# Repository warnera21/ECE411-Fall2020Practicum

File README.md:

# ECE411-Fall2020Practicum
This project is based in adding security and ease of access trough a door using Facial Recognition and RFID technologies. The implementation of keeping track of how many (Authorized) user go inside/out of a building is an extra feature that can aid with companies enforcing distancing strategies for COVID purposes. 

### TEAM 8: Hamed AlSaegui, Anthony Warner, Josh Pradera and Tamar Stigler-Flores.

### Arduino Code

	==> if the code is not uploaded yet
		the file (411.ino) must be inside a folder named (411)
		Follow the ... for board connections
		compile and upload the programm to the ATMega chip.
		
	==> used libraries
		SPI.h
		MFRC522.h
		LiquidCrystal_I2C.h
		Wire.h
	==> High Level Diagram Code
		set the LCD address to 0x27 for a 16 chars and 2 line display
		initialize the lcd
		initialize counter
		initialize receiveEvent function
			receive byte as a character
		VOID SETUP
			Initiate I2C communication
			Initiate  address bus designated to I2C with Raspberry Pi
			Initiate each MFRC522 card
			Join I2C bus as slave with address 8
				Call receiveEvent when data received 
			initialize output pins
		VOID LOOP
			be ready to scan a tag
				if scanned to ENTER (RFID1)
					If Tag is Valid
						AUTHORIZED
					If Tag is Not Valid
						UNAUTHORIZED
				if scanned to EXIT (RFID2)
					If Tag is Valid
						AUTHORIZED
					If Tag is Not Valid
						UNAUTHORIZED

### Raspberry Pi Code (Python Script)

	==> The sequence of the Face Recognition code goes as follow:
		1 - Collect the data set of pictures from each user.
		==> Used libraries: 
		    cv2 (openCV)
		    numpy
		 ==> Use the CascadeClassifier and load haarcascade_frontal_default.xml (used for the detection of faces)
		     Setup the raspberry pi camera
		     Setup input variable to assign an specific User ID (as a number)
		     WHILE TRUE
		     		Read from the raspberry pi camera.
				Set a onvertion for the photos from RGB to Gray Scale.
				Detect the face from the user.
				Increase the sampleNum variable by 1 as the picture samples are taken.
				Open window with video feed and also draw a rectangle on the detected face.
				Save 20 pictures in a folder named dataSet.
				When done break the LOOP.
		    Release the camera.
		    Destroy all the windows opened by the program.
		    
		    2- Train the data and create a file named trainingData.yml that will be used to recognize an user.
		       The .yml file contains  the serialized data for specific users.
		   ==> Used libraries:
		       os 
		       cv2
		       numpy
		       from PIL import Image (for manipulation of Images)
		       Create variable recognizer and call the function to create a Local Binary Operator.
		       	-  LBPH is used to extract features from an input image and match them with the faces in system's database.
		       Set the dataSet path.
		       Create  two arrays. One name faces and another names IDs.
		      		 Execute a for loop that will loop as many times as the amount of images that we have in the dataSet folder.
		      		 Convert images in monochromo format.
		      		 Convert images into a numpy array with name faceImg.
		      		 Extract ID from the name of the image and add it to the array IDs and add the data to the array faces.
		       Train the data set.
		       Save the .yml file inside recognizer folder.
		       Destroy all the windows opened by the program.
		       
		    3- Recognize a face an open the door.
		    ==> Used libraries:
		        numpy
			cv2
			time
			from smbus import SMBus (I2C communication)
		        Specify bus address used for I2C.
			Setup the CascadeClassifier function with the haarcascade_frontalface_default.xml
			Setup Raspberry Pi camera.
			Create a variable named rec and use the Local Binary Operator function.
			Load the trained data present in the .yml file.
			Initiate id to 0
			Create a solenoid function for the I2C communication between Raspberry Pi and Arduino.
				Write a byte 0x1 using bus address 0x8 to unlock the door.
				Wait for 5 seconds.
				Write a byte 0x0 using the same bus address  to Lock the door.
				
			While True
				Read from Raspberry Pi camera.
				Convert pictures from Color to Gray Scale.
				Set a Multiscale to compensate from faces closer and far away from the camera.
			        For LOOP 
					Start the prediction of the user based in the trained data and the face detected using the haar cascade file.
					Compare faces detected to IDs .
					If the ID and face detected match, release the camera and set the camera again for stability issues with the time library.
						Print the user Name in the terminal for testing purposes.
						Call the solenoid function and send  a 0x1 bit to the Arduino over I2C to unlock door.
						Wait for 5 seconds. 
						Send  a 0x0 bit to the Arduino to lock the door.
					ELSE IF ID dosnt match the trained data set.
						Print Unauthorized user in the terminal for testing purposes.
						Release the camera.
						Setup the camera. 
						
				Brake out of the program with cntrl+C. 
				Release the camera.
				Destroy all the windows created by the program.

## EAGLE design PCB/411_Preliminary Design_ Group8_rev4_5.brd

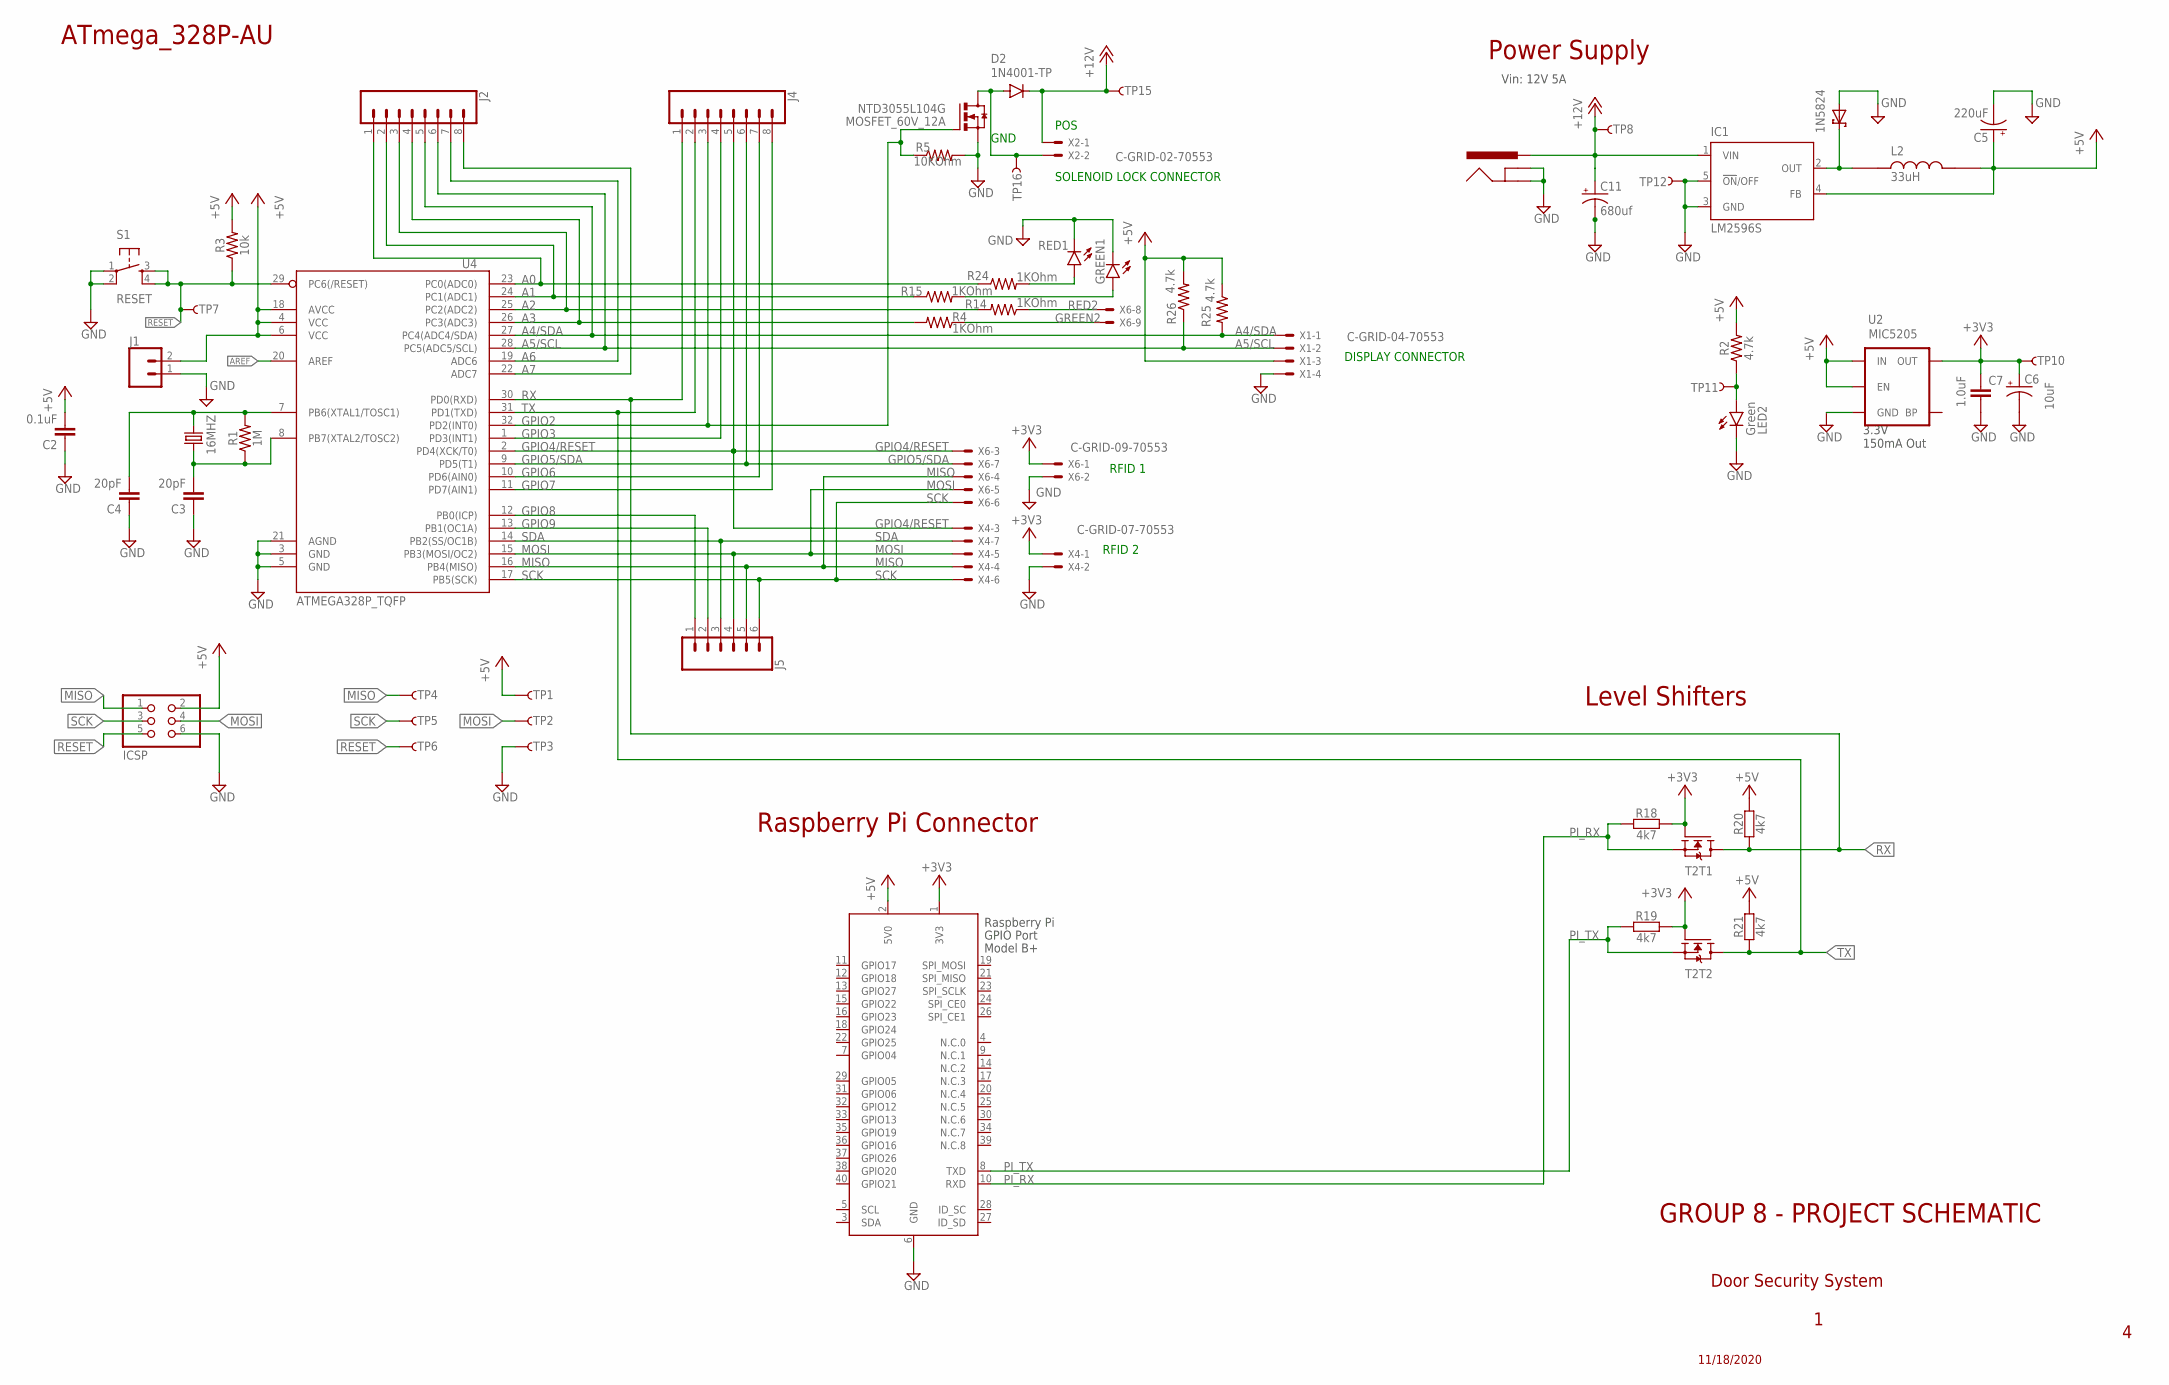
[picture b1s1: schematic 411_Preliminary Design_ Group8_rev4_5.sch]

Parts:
1N5824: SCHOTTKY-DIODECB429-15; CB429-15
16MHZ: 16MHZ; HC49/S
C2: 0.1uF; 0603
C3, C4: 20pF; 0603
C5: 220uF; 153CLV-0605
C6: 10uF; EIA3216
C7: 1.0uF; 0603
C11: 680uf; 153CLV-0605
D2: 1N4001-TP; DO41-10
GREEN1: LED5MM
IC1: LM2596S; TO263-5
ICSP: ICSP; 2X03
J1: CONN_02; 1X02
J2, J4: CONN_08"; 1X08
J3: POWER_JACKSUPER_BOMB_DIGITY; POWER_JACK_SMD_OVERPASTE_SUPER_BOMB_DIGITY
J5: CONN_06SILK_FEMALE_PTH; 1X06
L2: 33uH; IND_#B953AS-330M=P3
LED2: Green; LED-1206
MOSFET_60V_12A: NTD3055L104G; DPAK3
R1: 1M; 0603
R2, R25, R26: 4.7k; 0603
R3: 10k; 0603
R4, R14, R15, R24: 1KOhm; M1406
R5: 10KOhm; M1406
R18, R19, R20, R21: 4k7; C0402
RED1: LED5MM
S1: RESET; TACTILE-SWITCH-SMD
T2: BSS138PS; SOT363
TP1, TP2, TP3, TP4, TP5, TP6, TP7, TP8, TP10, TP11, TP12, TP15, TP16: TP-3x5; PAD.03X.05
U2: MIC5205; SOT23-5
U4: ATMEGA328P_TQFP; TQFP32-08
X1: C-GRID-04-70553; 70553-04
X2: C-GRID-02-70553; 70553-02
X4: C-GRID-07-70553; 70553-07
X5: RASPI_BOARD_B+_E4P; RASPI_BOARD_B+_EDGES_4DRILL_PAD
X6: C-GRID-09-70553; 70553-09

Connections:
+3V3: C6.+, C7.1, R18.2, R19.2, T2.2 (G), T2.5 (G), TP10.P$1, U2.5 (OUT), X4.1, X5.1 (3V3), X6.1
+5V: C2.2, C5.+, IC1.4 (FB), ICSP.2, J1.2, L2.2, R2.2, R3.2, R20.2, R21.2, R25.1, R26.2, TP1.P$1, U2.1 (IN), U2.3 (EN), U4.4 (VCC), U4.6 (VCC), U4.18 (AVCC), X1.3, X5.2 (5V0)
+12V: C11.+, D2.C, IC1.1 (VIN), J3.VIN0 (PWR), TP8.P$1, TP15.P$1, X2.1
A0: J2.1, R24.1, U4.23 (PC0(ADC0))
A1: J2.2, R15.1, U4.24 (PC1(ADC1))
A2: J2.3, R14.2, U4.25 (PC2(ADC2))
A3: J2.4, R4.2, U4.26 (PC3(ADC3))
A4/SDA: J2.5, R25.2, U4.27 (PC4(ADC4/SDA)), X1.1
A5/SCL: J2.6, R26.1, U4.28 (PC5(ADC5/SCL)), X1.2
A6: J2.7, U4.19 (ADC6)
A7: J2.8, U4.22 (ADC7)
AREF: U4.20 (AREF)
GND: 1N5824.A, C2.1, C3.1, C4.1, C5.-, C6.-, C7.2, C11.-, GREEN1.K (C), IC1.3 (GND), IC1.5 (!ON!/OFF), ICSP.6, J1.1, J3.GND (GNDBREAK), J3.P$4 (GND), LED2.C, MOSFET_60V_12A.2 (S), R5.2, RED1.K (C), S1.1, S1.2, TP3.P$1, TP12.P$1, U2.2 (GND), U4.3 (GND), U4.5 (GND), U4.21 (AGND), X1.4, X4.2, X5.6 (GND), X6.2
GPIO2: J4.3, MOSFET_60V_12A.1 (G), R5.1, U4.32 (PD2(INT0))
GPIO3: J4.4, U4.1 (PD3(INT1))
GPIO4/RESET: J4.5, U4.2 (PD4(XCK/T0)), X4.3, X6.3
GPIO5/SDA: J4.6, U4.9 (PD5(T1)), X6.7
GPIO6: J4.7, U4.10 (PD6(AIN0))
GPIO7: J4.8, U4.11 (PD7(AIN1))
GPIO8: J5.1, U4.12 (PB0(ICP))
GPIO9: J5.2, U4.13 (PB1(OC1A))
GREEN2: R4.1, X6.9
MISO: ICSP.1, J5.5, TP4.P$1, U4.16 (PB4(MISO)), X4.4, X6.4
MOSI: ICSP.4, J5.4, TP2.P$1, U4.15 (PB3(MOSI/OC2)), X4.5, X6.5
unnamed: 1N5824.C, IC1.2 (OUT), L2.1
unnamed: LED2.A, R2.1, TP11.P$1
unnamed: 16MHZ.2, C4.2, R1.2, U4.7 (PB6(XTAL1/TOSC1))
unnamed: 16MHZ.1, C3.2, R1.1, U4.8 (PB7(XTAL2/TOSC2))
unnamed: D2.A, MOSFET_60V_12A.3 (D), TP16.P$1, X2.2
unnamed: GREEN1.A, R15.2
unnamed: R24.2, RED1.A
PI_RX: R18.1, T2.1 (S), X5.10 (RXD)
PI_TX: R19.1, T2.4 (S), X5.8 (TXD)
RED2: R14.1, X6.8
RESET: ICSP.5, R3.1, S1.3, S1.4, TP6.P$1, TP7.P$1, U4.29 (PC6(/RESET))
RX: J4.1, R20.1, T2.6 (D), U4.30 (PD0(RXD))
SCK: ICSP.3, J5.6, TP5.P$1, U4.17 (PB5(SCK)), X4.6, X6.6
SDA: J5.3, U4.14 (PB2(SS/OC1B)), X4.7
TX: J4.2, R21.1, T2.3 (D), U4.31 (PD1(TXD))

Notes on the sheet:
ATmega_328P-AU
RFID 1
RFID 2
DISPLAY CONNECTOR
SOLENOID LOCK CONNECTOR
GND
POS
Door Security System
GROUP 8 - PROJECT SCHEMATIC
11/18/2020
Level Shifters
Power Supply
3.3V 150mA Out
Vin: 12V 5A
Raspberry Pi Connector

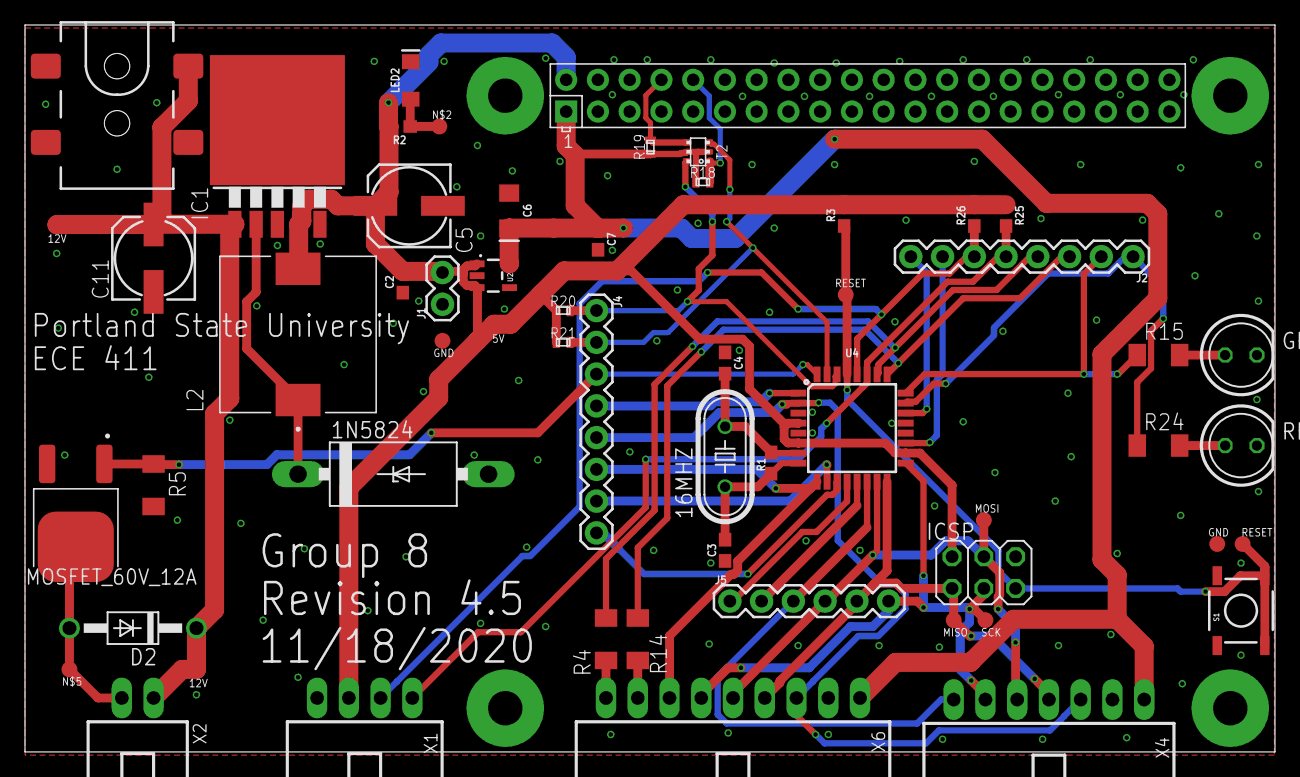
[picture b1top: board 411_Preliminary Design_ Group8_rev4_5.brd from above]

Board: 2 copper layers, 100.0 x 58.2 mm, 58 parts (0 on the bottom side), 38 nets.

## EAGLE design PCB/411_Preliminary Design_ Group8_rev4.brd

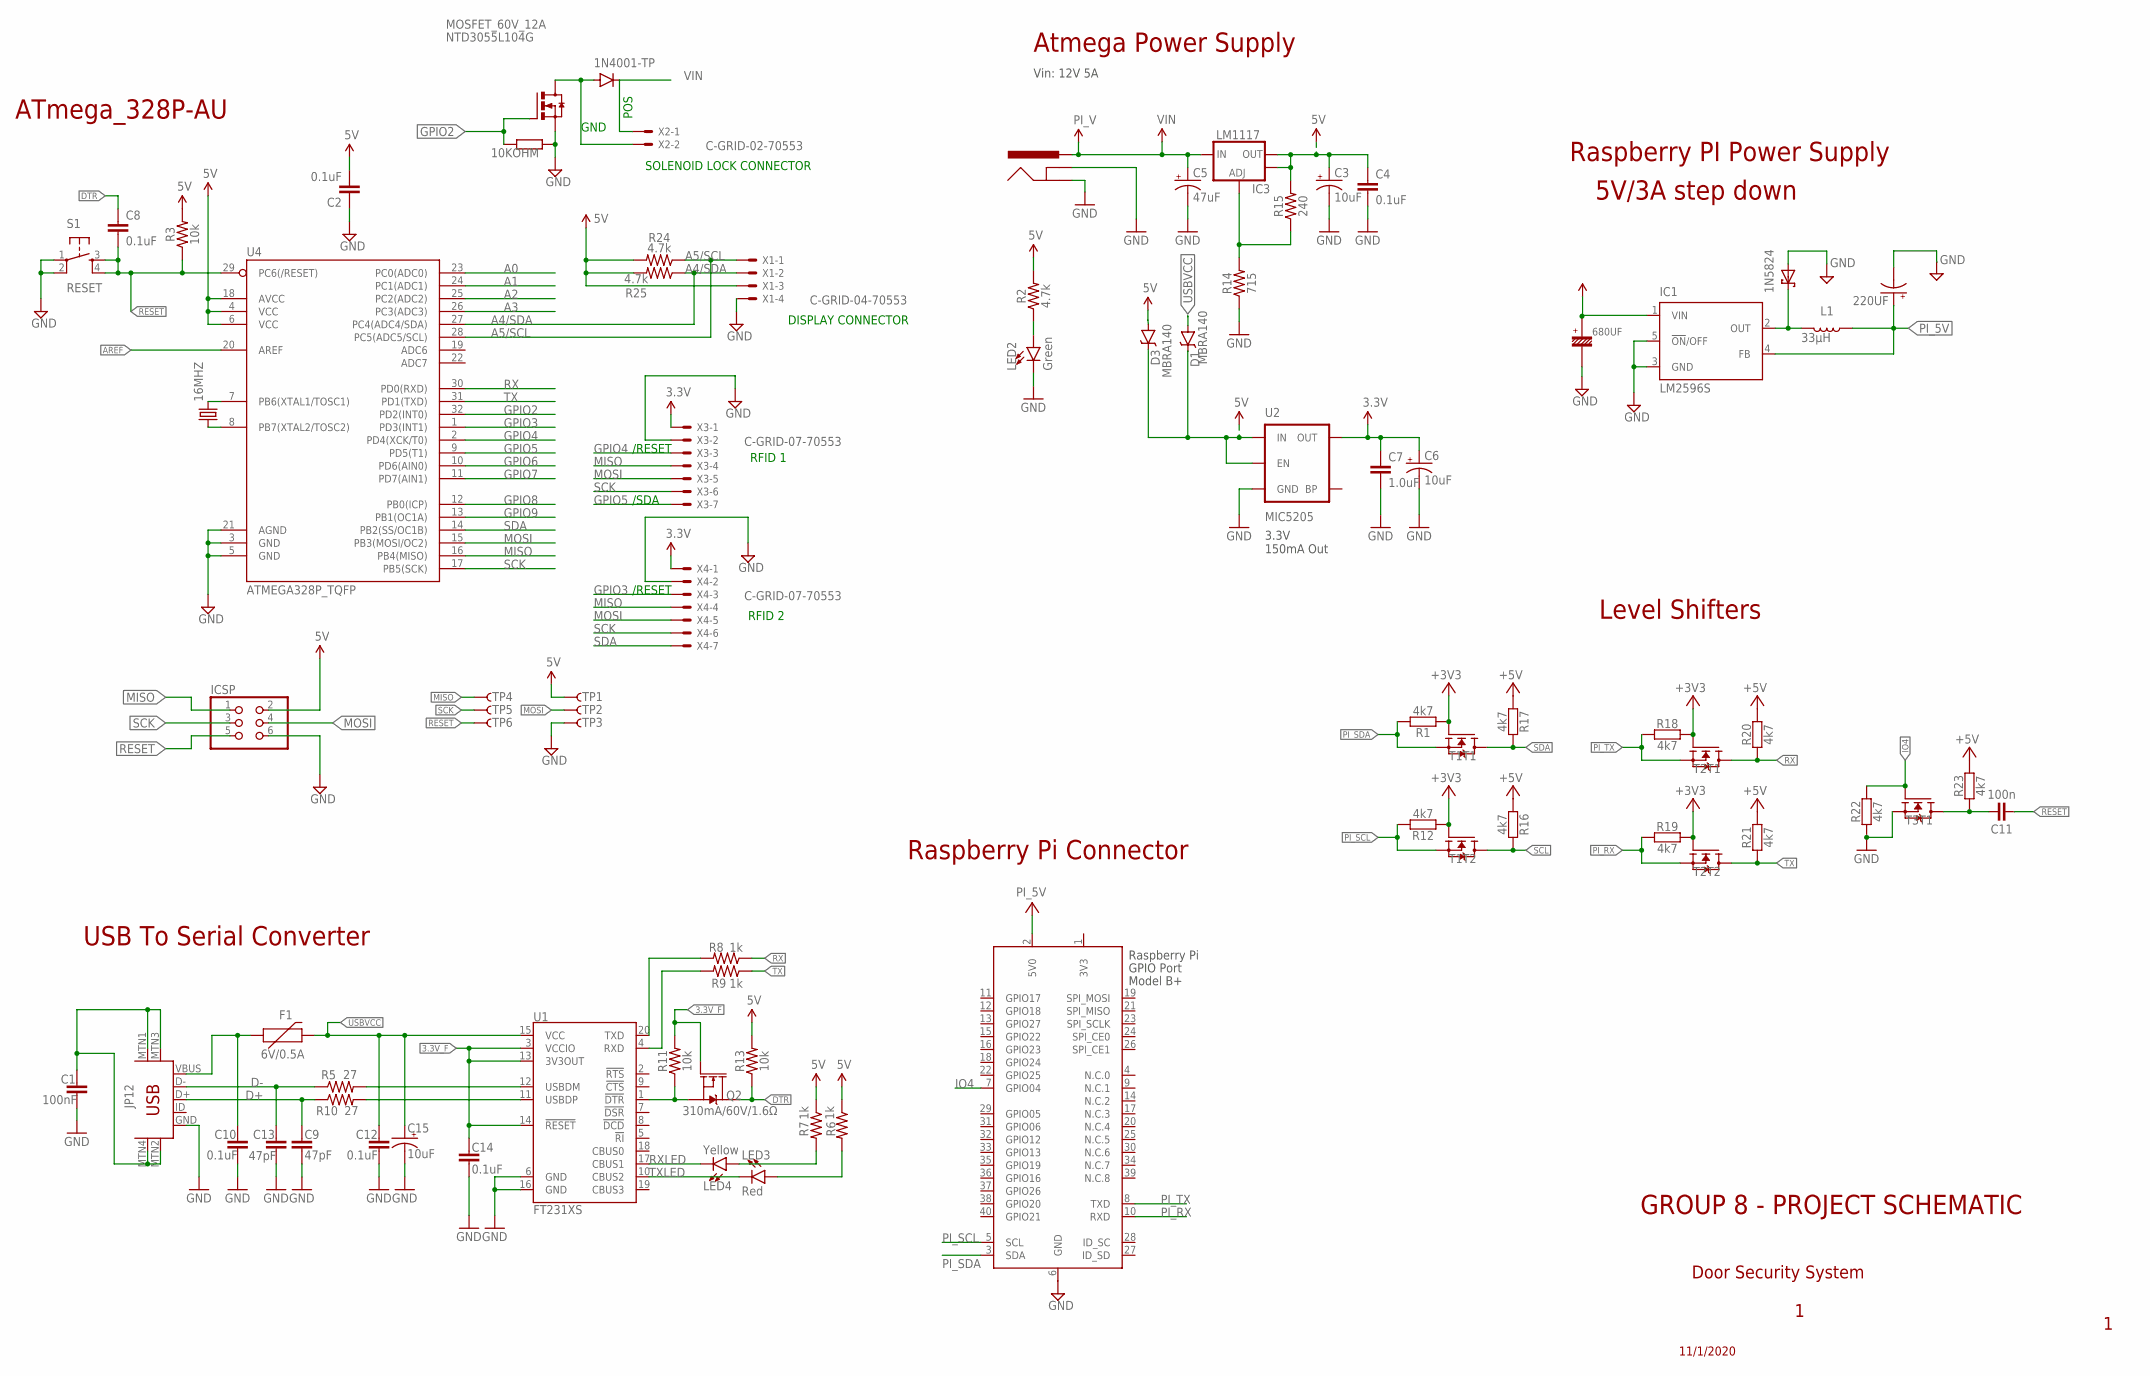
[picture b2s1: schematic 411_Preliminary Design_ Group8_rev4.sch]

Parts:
1N5824: SCHOTTKY-DIODECB429-15; CB429-15
16MHZ: CRYSTALHC49S; HC49/S
220UF: CPOL-US139CLL-2R; 139CLL-2R
680UF: CE-16V-10-5.08; 16V-10-5.08
C1: 100nF; 0603
C2, C4, C8, C10, C12, C14: 0.1uF; 0603
C3, C6, C15: 10uF; EIA3216
C5: 47uF; PANASONIC_D
C7: 1.0uF; 0603
C9, C13: 47pF; 0603
C11: 100n; C0402
D1, D3: MBRA140; SMA-DIODE
F1: 6V/0.5A; 1206
IC1: LM2596S; TO263-5
IC3: LM1117; SOT223-ALT1
ICSP: PINHD-2X3; 2X03
J3: POWER_JACKSUPER_BOMB_DIGITY; POWER_JACK_SMD_OVERPASTE_SUPER_BOMB_DIGITY
JP12: USB-MINIB-5PIN; USB-MINIB
L1: 33µH; 0805
LED2: Green; LED-1206
LED3: Red; LED-1206
LED4: Yellow; LED-1206
MOSFET_60V_12A: NTD3055L104G; DPAK3
Q2: 310mA/60V/1.6Ω; SOT323
R1, R12, R16, R17, R18, R19, R20, R21, R22, R23: 4k7; C0402
R2, R24, R25: 4.7k; 0603
R3, R11, R13: 10k; 0603
R5, R10: 27; 0603
R6, R7, R8, R9: 1k; 0603
R14: 715; 0603
R15: 240; 0603
S1: RESET; TACTILE-SWITCH-SMD
T1, T2, T3: BSS138PS; SOT363
TP1, TP2, TP3, TP4, TP5, TP6: TP-3x5; PAD.03X.05
U1: FT231XS; SSOP20_L
U2: MIC5205; SOT23-5
U4: ATMEGA328P_TQFP; TQFP32-08
X1: C-GRID-04-70553; 70553-04
X2: C-GRID-02-70553; 70553-02
X3, X4: C-GRID-07-70553; 70553-07
X5: RASPI_BOARD_B+_E4P; RASPI_BOARD_B+_EDGES_4DRILL_PAD

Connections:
3.3V: C6.+, C7.1, U2.5 (OUT), X3.1, X4.1
3.3V_F: C14.1, Q2.1 (G), R11.2, U1.3 (VCCIO), U1.13 (3V3OUT), U1.14 (!RESET)
3V3: X5.1 (3V3)
5V: 680UF.+, C2.2, C3.+, C4.1, D1.C, D3.A, D3.C, IC1.1 (VIN), IC3.2 (OUT), IC3.4 (OUT), ICSP.2, R2.2, R3.2, R6.1, R7.1, R13.2, R15.2, R24.2, R25.2, TP1.P$1, U2.1 (IN), U2.3 (EN), U4.4 (VCC), U4.6 (VCC), U4.18 (AVCC), X1.3
+3V3: R1.1, R12.1, R18.2, R19.2, T1.2 (G), T1.5 (G), T2.2 (G), T2.5 (G)
+5V: R16.1, R17.1, R20.2, R21.2, R23.2
A0: U4.23 (PC0(ADC0))
A1: U4.24 (PC1(ADC1))
A2: U4.25 (PC2(ADC2))
A3: U4.26 (PC3(ADC3))
A4/SDA: R25.1, U4.27 (PC4(ADC4/SDA)), X1.2
A5/SCL: R24.1, U4.28 (PC5(ADC5/SCL)), X1.1
AREF: U4.20 (AREF)
D0_RX1: C11.2, R23.1, T3.6 (D)
D+: C9.1, JP12.D+, R10.1
D-: C13.1, JP12.D-, R5.1
DTR: C8.1, Q2.3 (D), R13.1
FTDI_DTR: Q2.2 (S), R11.1, U1.1 (!DTR)
GND: 1N5824.A, 220UF.-, 680UF.-, C1.2, C2.1, C3.-, C4.2, C5.-, C6.-, C7.2, C9.2, C10.2, C12.2, C13.2, C14.2, C15.-, IC1.3 (GND), IC1.5 (!ON!/OFF), ICSP.6, J3.GND (GNDBREAK), J3.P$4 (GND), JP12.GND, LED2.C, MOSFET_60V_12A.2 (S), R14.1, R22.1, S1.1, S1.2, T3.1 (S), TP3.P$1, U1.6 (GND), U1.16 (GND), U2.2 (GND), U4.3 (GND), U4.5 (GND), U4.21 (AGND), X1.4, X3.2, X4.2, X5.6 (GND)
GPIO2: MOSFET_60V_12A.1 (G), U4.32 (PD2(INT0))
GPIO3: U4.1 (PD3(INT1)), X4.3
GPIO4: U4.2 (PD4(XCK/T0)), X3.3
GPIO5: U4.9 (PD5(T1)), X3.7
GPIO6: U4.10 (PD6(AIN0))
GPIO7: U4.11 (PD7(AIN1))
GPIO8: U4.12 (PB0(ICP))
GPIO9: U4.13 (PB1(OC1A))
IO4: R22.2, T3.2 (G), X5.7 (GPIO04)
MISO: ICSP.1, TP4.P$1, U4.16 (PB4(MISO)), X3.4, X4.4
MOSI: ICSP.4, TP2.P$1, U4.15 (PB3(MOSI/OC2)), X3.5, X4.5
unnamed: 1N5824.C, IC1.2 (OUT), L1.2
unnamed: LED2.A, R2.1
unnamed: 16MHZ.2, U4.7 (PB6(XTAL1/TOSC1))
unnamed: 16MHZ.1, U4.8 (PB7(XTAL2/TOSC2))
unnamed: MOSFET_60V_12A.3 (D), X2.2
unnamed: R5.2, U1.12 (USBDM)
unnamed: R10.2, U1.11 (USBDP)
unnamed: LED3.A, R6.2
unnamed: LED4.A, R7.2
unnamed: IC3.1 (ADJ), R14.2, R15.1
unnamed: C1.1, JP12.MTN1 (MTN2), JP12.MTN2 (MTN3), JP12.MTN3 (MTN1), JP12.MTN4
PI_5V: 220UF.+, IC1.4 (FB), L1.1, X5.2 (5V0)
PI_RX: R19.1, T2.4 (S), X5.10 (RXD)
PI_SCL: R12.2, T1.4 (S), X5.5 (SCL)
PI_SDA: R1.2, T1.1 (S), X5.3 (SDA)
PI_TX: R18.1, T2.1 (S), X5.8 (TXD)
RESET: C8.2, C11.1, ICSP.5, R3.1, S1.3, S1.4, TP6.P$1, U4.29 (PC6(/RESET))
RX: R8.1, R20.1, T2.6 (D), U4.30 (PD0(RXD))
RXD: R9.2, U1.4 (RXD)
RXLED: LED4.C, U1.17 (CBUS1)
SCK: ICSP.3, TP5.P$1, U4.17 (PB5(SCK)), X3.6, X4.6
SCL: R16.2, T1.3 (D)
SDA: R17.2, T1.6 (D), U4.14 (PB2(SS/OC1B)), X4.7
TX: R9.1, R21.1, T2.3 (D), U4.31 (PD1(TXD))
TXD: R8.2, U1.20 (TXD)
TXLED: LED3.C, U1.10 (CBUS2)
USBVCC: C12.1, C15.+, D1.A, F1.2, U1.15 (VCC)
VIN: C5.+, IC3.3 (IN), J3.VIN0 (PWR), X2.1
VUSB: C10.1, F1.1, JP12.VBUS

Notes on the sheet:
Atmega Power Supply
ATmega_328P-AU
USB To Serial Converter
3.3V 150mA Out
Vin: 12V 5A
RFID 1
RFID 2
SDA
DISPLAY CONNECTOR
SOLENOID LOCK CONNECTOR
1N4001-TP
GND
POS
/RESET
/SDA
Door Security System
GROUP 8 - PROJECT SCHEMATIC
11/1/2020
Level Shifters
Raspberry PI Power Supply
5V/3A step down
Raspberry Pi Connector

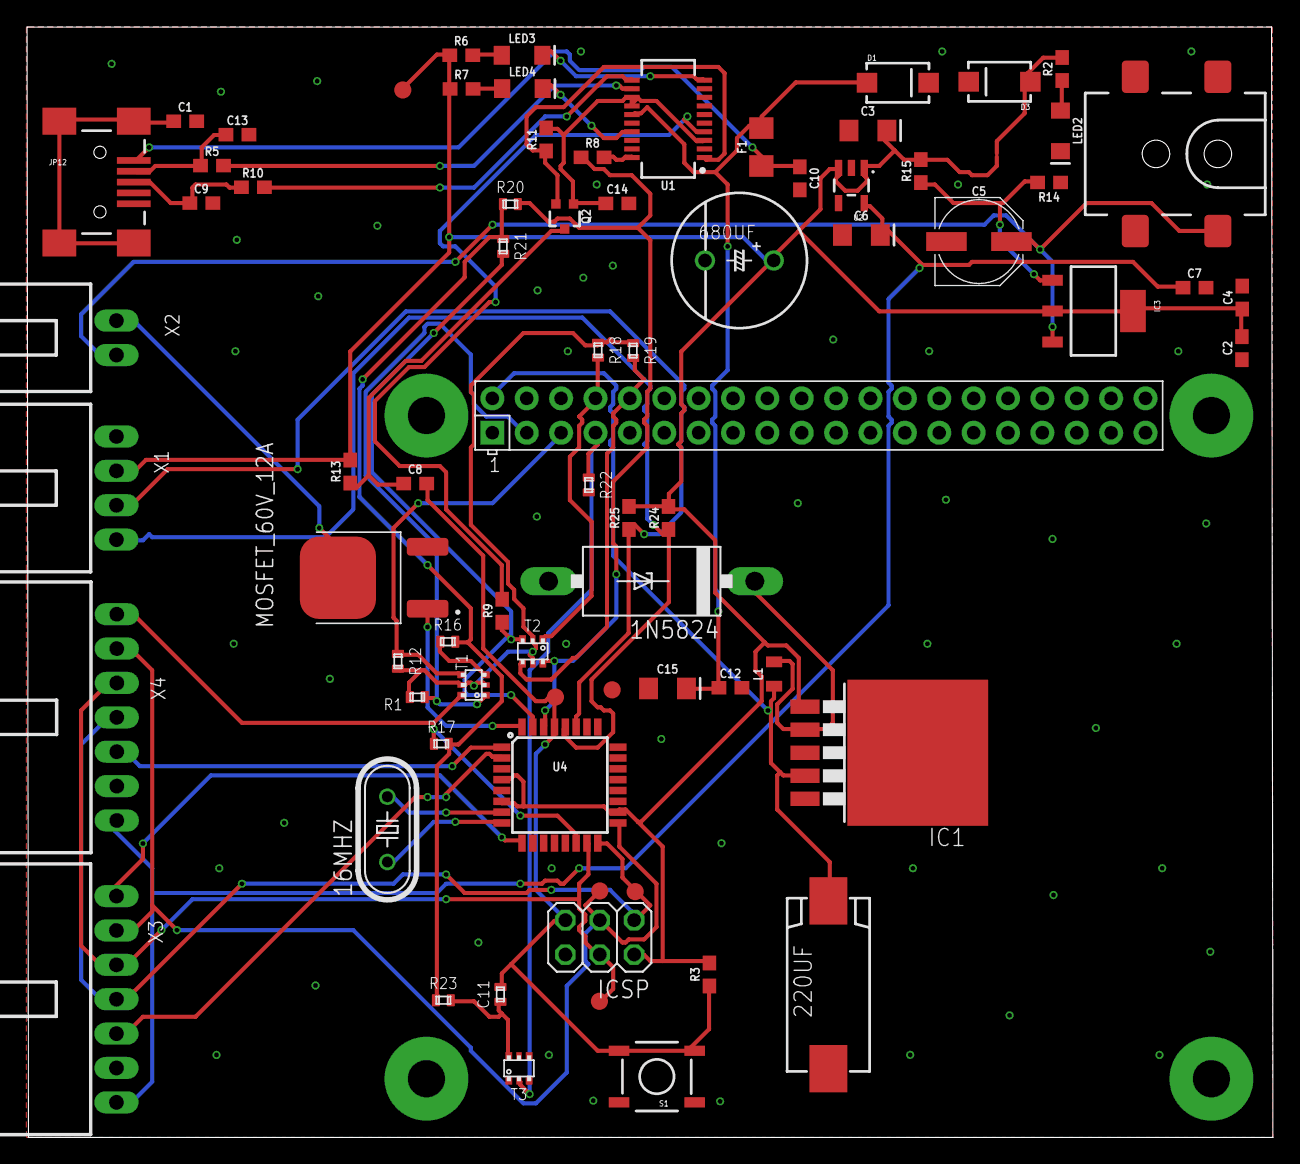
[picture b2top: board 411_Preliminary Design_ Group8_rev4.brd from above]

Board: 2 copper layers, 92.1 x 82.0 mm, 75 parts (0 on the bottom side), 49 nets.

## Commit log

2020-11-02 Add files via upload
    First Revision of our Project's schematic
2020-11-02 Create Nov 2 2020 HW4
2020-11-02 Add files via upload
    Breadboard setup of our preliminary schematic
2020-11-02 Update Nov 2 2020 HW4
2020-11-02 Rename Nov 2 2020 HW4 to Nov 2 2020 HW4.md
2020-11-02 Create Folder
2020-11-09 added Preliminary Design Revision 2
2020-11-09 Add files via upload
    Preliminary board layout for PCB, Revision 2
2020-11-14 Project Timeline Upload
2020-11-15 Updated PCB
2020-11-19 Update Board Layout and Schematic
2020-11-19 Updating layout
2020-11-19 PDS Version 1
2020-11-30 uploaded both codes
2020-11-30 needed folders for face recognition
2020-12-01 Create Reviews
2020-12-02 Breadboard Testing Image
2020-12-02 Updated BOM Items
2020-12-02 Design Notes from Team 16
2020-12-04 updated arduino code
2020-12-04 updated Raspberry code
2020-12-04 Add files via upload
    I2C communication Raspberry/Arduino
2020-12-04 Add files via upload
    I2C approach communication Raspberry/Arduino
2020-12-06 Arduino README
2020-12-07 Added PDS V3
2020-12-07 Updated LEVEL-1 Diagram
2020-12-08 Add files via upload
    Updated PDS revision 4

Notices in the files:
parts and their libraries:
SparkFun-Capacitors: Licensing: CC v3.0 Share-Alike You are welcome to use this library for commercial purposes.
SparkFun-DiscreteSemi: Licensing: Creative Commons ShareAlike 4.0 International - https://creativecommons.org/licenses/by-sa/4.0
